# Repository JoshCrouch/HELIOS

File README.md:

# HELIOS
A basic SDR Project to practice designing an RF Front-End

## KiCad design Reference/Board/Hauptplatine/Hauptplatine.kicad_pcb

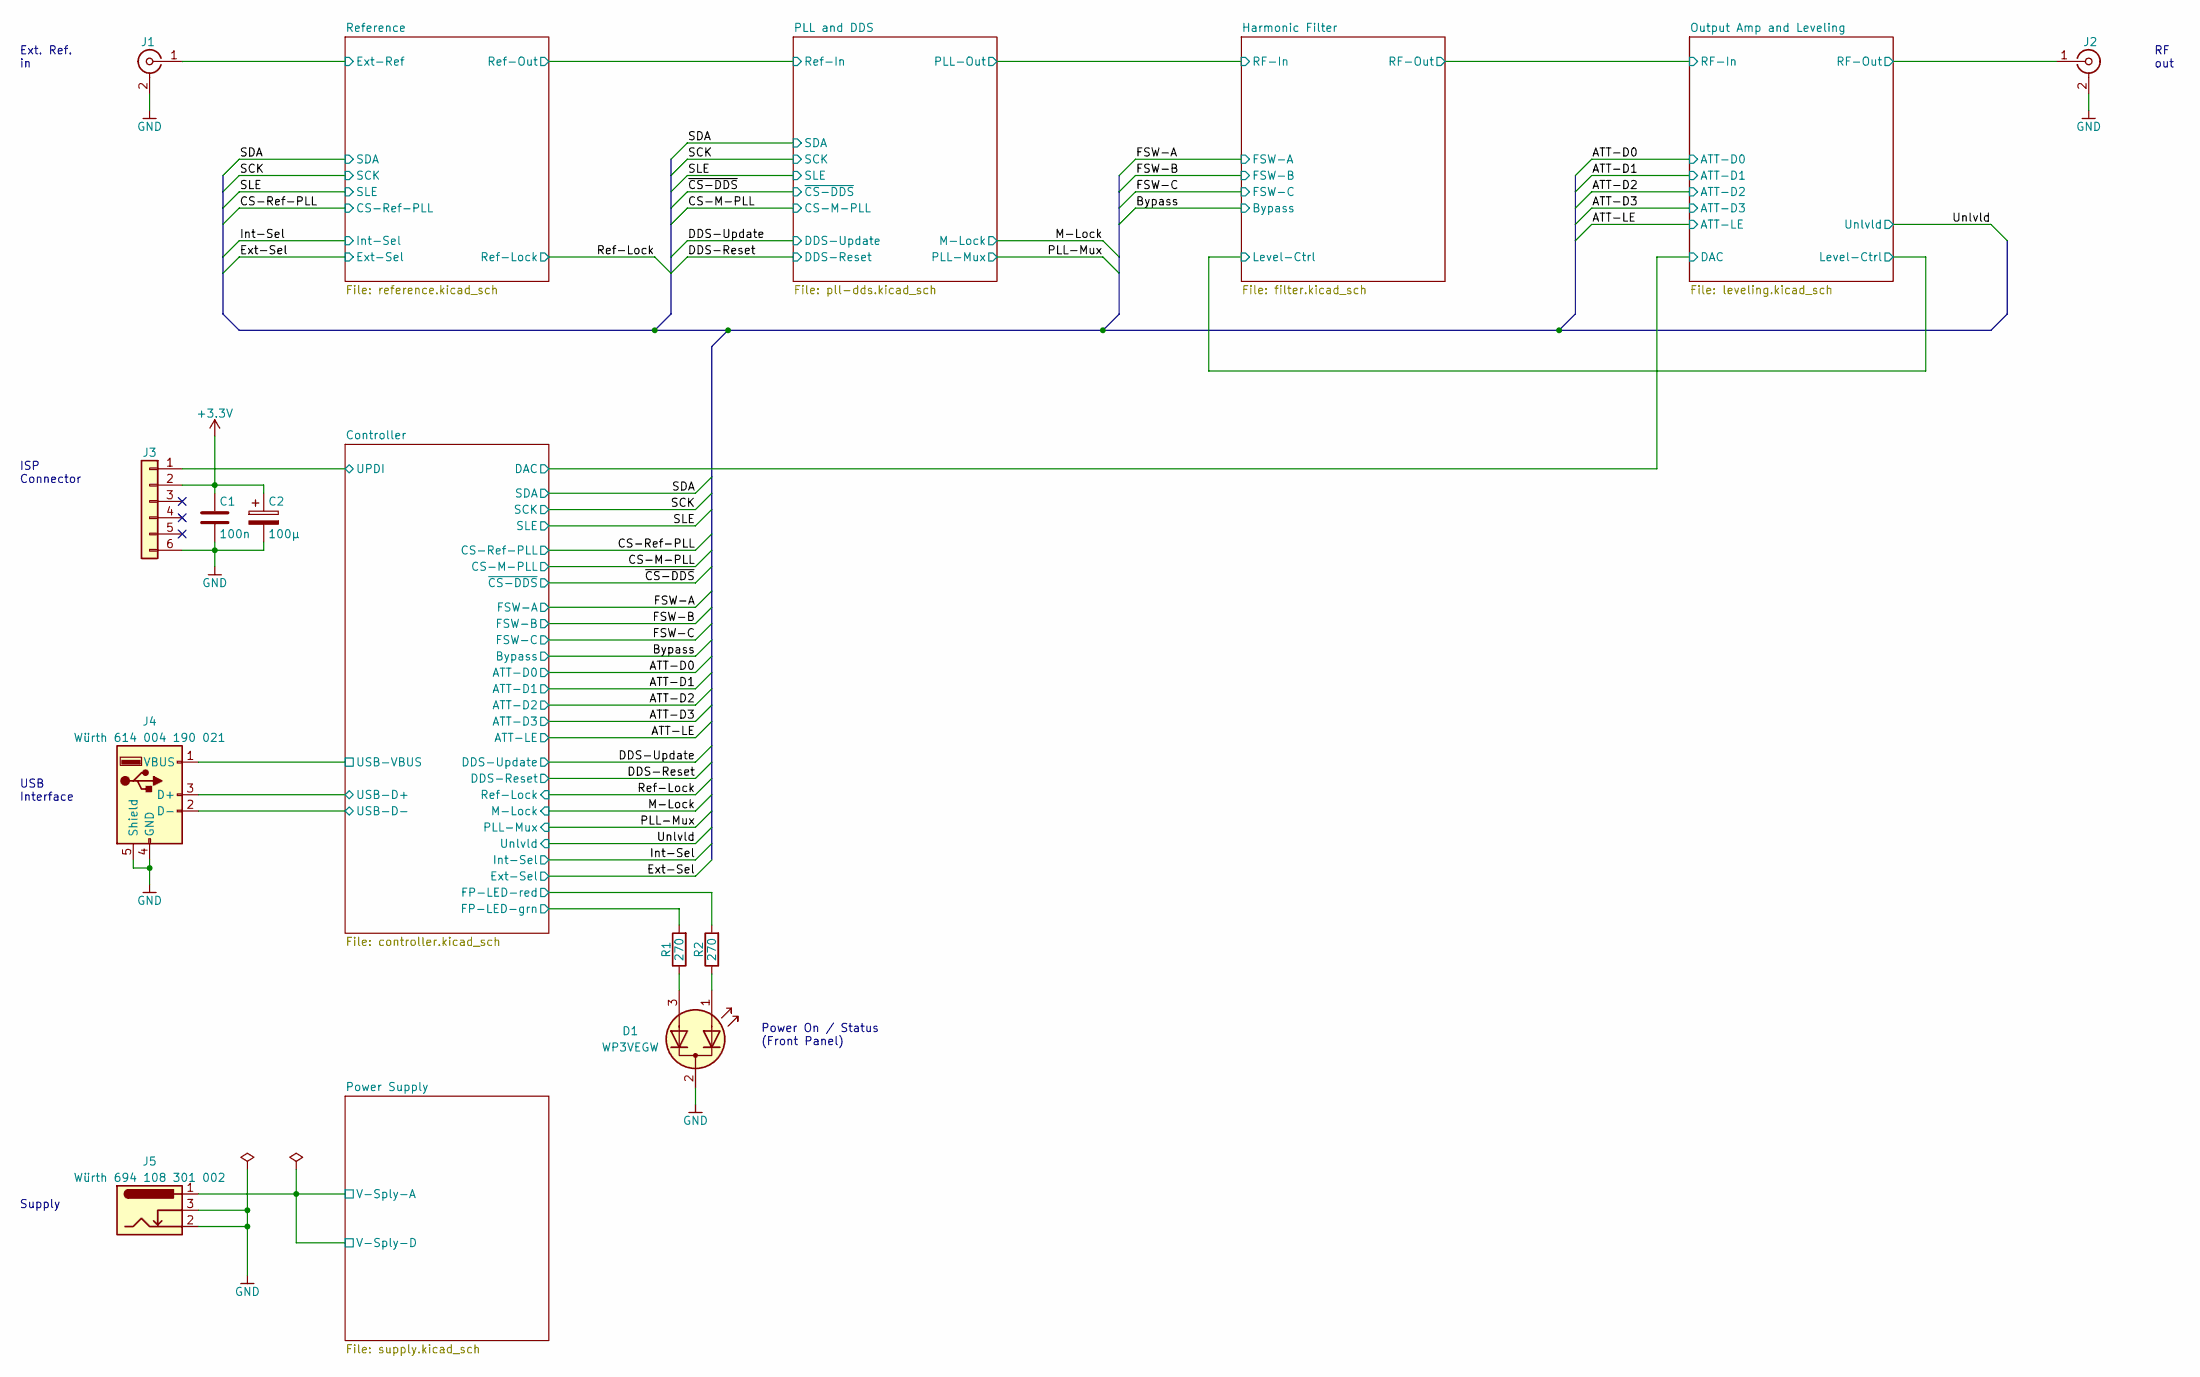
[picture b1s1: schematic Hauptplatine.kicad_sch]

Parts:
C1: 100n; C_0805_2012Metric
C2: 100µ; CP_Radial_D6.3mm_P2.50mm
D1: WP3VEGW; LED_D3.0mm-3
J1: SMA; SMA-Jack_angle
J2: Cinch 142-0781-821; SMA-Launcher_Cinch_142-0771-831
J3: Conn_01x06; IDC-Header_2x03_P2.54mm_Vertical
J4: Würth 614 004 190 021; USB_A_Stewart_SS-52100-001_Horizontal
J5: Würth 694 108 301 002; BarrelJack_Wuerth_6941xx301002
R1, R2: 270; R_0805_2012Metric

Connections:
/Controller/FP-LED-grn: R1.2; also elsewhere on the board
/Controller/FP-LED-red: R2.2; also elsewhere on the board
/Controller/UPDI: J3.1; also elsewhere on the board
/Controller/USB-D+: J4.3 (D+); also elsewhere on the board
/Controller/USB-D-: J4.2 (D-); also elsewhere on the board
/Controller/USB-VBUS: J4.1 (VBUS); also elsewhere on the board
/Output Amp and Leveling/RF-Out: J2.1 (In); also elsewhere on the board
/Power Supply/V-Sply-A: J5.1; also elsewhere on the board
/Reference/Ext-Ref: J1.1 (In); also elsewhere on the board
unnamed: D1.1 (A1), R2.1
unnamed: D1.3 (A2), R1.1

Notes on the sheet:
Supply
USB Interface
RF out
Power On / Status (Front Panel)
Ext. Ref. in
ISP Connector

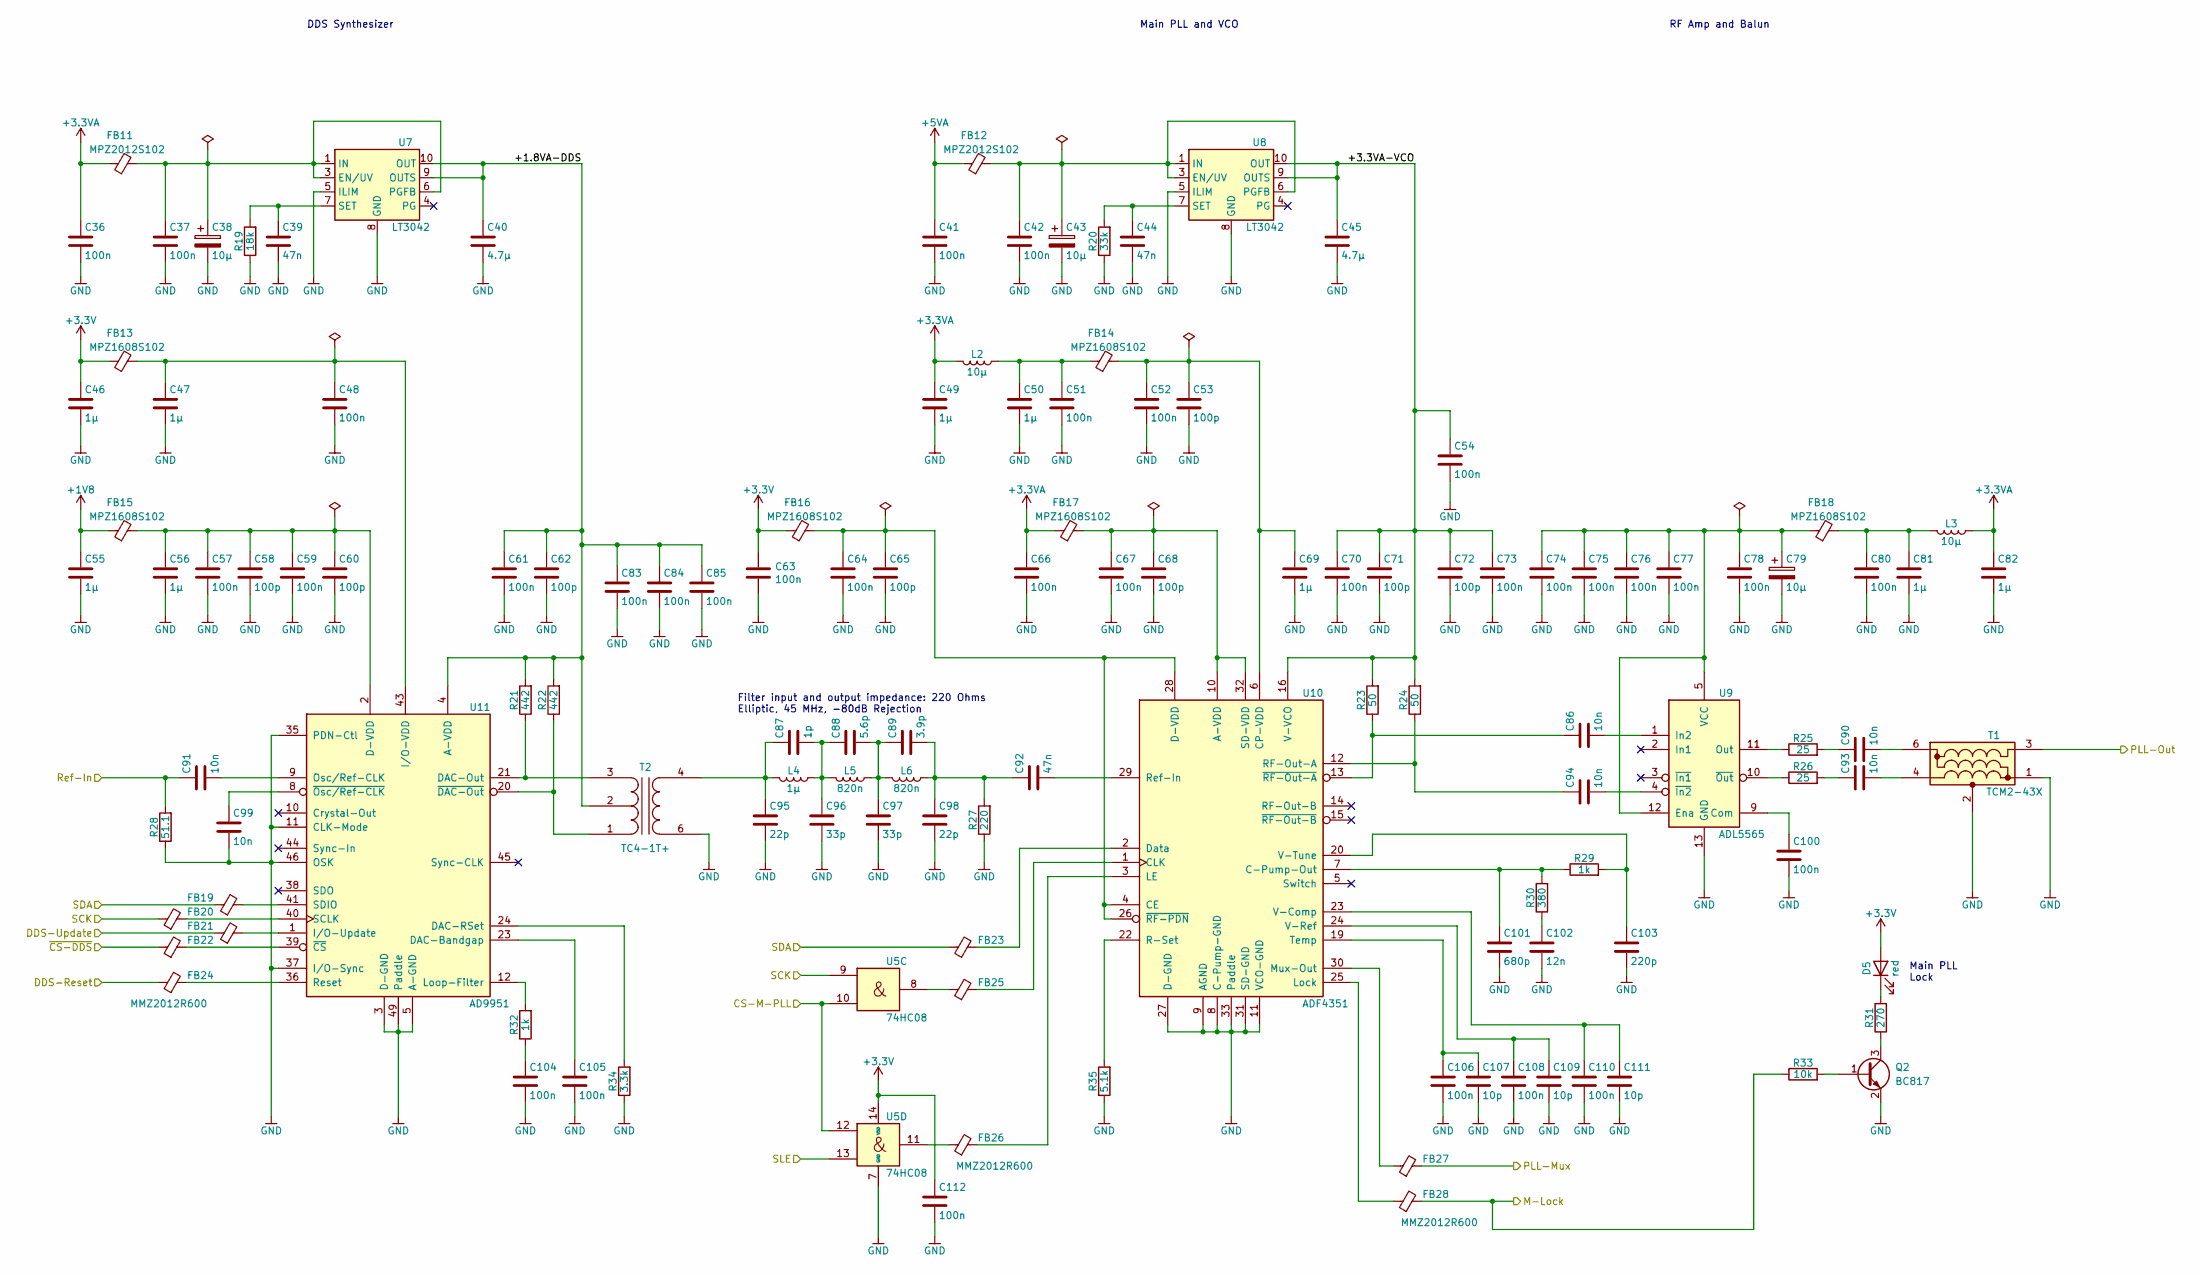
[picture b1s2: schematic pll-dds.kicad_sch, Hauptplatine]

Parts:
C36, C37, C41, C42, C112: 100n; C_0805_2012Metric
C38, C43, C79: 10µ; CP_EIA-3528-21_Kemet-B
C39, C44, C92: 47n; C_0805_2012Metric
C40, C45: 4.7µ; C_0805_2012Metric
C46, C47, C49, C50, C55, C56, C81, C82: 1µ; C_0603_1608Metric
C48, C51, C52, C54, C57, C59, C61, C63, C64, C66, C67, C70, C73, C74, C75, C76, C77, C78, C80, C83, C84, C85, C100, C104, C105, C106, C108, C110: 100n; C_0603_1608Metric
C53, C58, C60, C62, C65, C68, C71, C72: 100p; C_0603_1608Metric
C69: 1µ; C_0805_2012Metric
C86, C90, C91, C93, C94, C99: 10n; C_0603_1608Metric
C87: 1p; C_0805_2012Metric
C88: 5.6p; C_0805_2012Metric
C89: 3.9p; C_0805_2012Metric
C95, C98: 22p; C_0805_2012Metric
C96, C97: 33p; C_0805_2012Metric
C101: 680p; C_0603_1608Metric
C102: 12n; C_0603_1608Metric
C103: 220p; C_0603_1608Metric
C107, C109, C111: 10p; C_0603_1608Metric
D5: red; LED_0805_2012Metric
FB11, FB12: MPZ2012S102; L_0805_2012Metric
FB13, FB14, FB15, FB16, FB17, FB18: MPZ1608S102; L_0603_1608Metric
FB19, FB20, FB21, FB22, FB23, FB24, FB25, FB26, FB27, FB28: MMZ2012R600; L_0805_2012Metric
L2, L3: 10µ; L_0805_2012Metric
L4: 1µ; L_0805_2012Metric
L5, L6: 820n; L_0805_2012Metric
Q2: BC817; SOT-23
R19: 18k; R_0805_2012Metric
R20: 33k; R_0805_2012Metric
R21, R22: 442; R_0603_1608Metric
R23, R24: 50; R_0603_1608Metric
R25, R26: 25; R_0603_1608Metric
R27: 220; R_0805_2012Metric
R28: 51.1; R_0603_1608Metric
R29, R32: 1k; R_0603_1608Metric
R30: 380; R_0603_1608Metric
R31: 270; R_0805_2012Metric
R33: 10k; R_0805_2012Metric
R34: 3.3k; R_0603_1608Metric
R35: 5.1k; R_0603_1608Metric
T1: TCM2-43X; Mini-Circuits_DB1627
T2: TC4-1T+; Mini-Circuits_AT224-1
U5: 74HC08; SOIC-14_3.9x8.7mm_P1.27mm
U7, U8: LT3042; MSOP-10-1EP_3x3mm_P0.5mm_EP1.68x1.88mm
U9: ADL5565; QFN-16-1EP_3x3mm_P0.5mm_EP1.45x1.45mm_ThermalVias
U10: ADF4351; QFN-32-1EP_5x5mm_P0.5mm_EP3.1x3.1mm_ThermalVias
U11: AD9951; TQFP-48-1EP_7x7mm_P0.5mm_EP3.5x3.5mm

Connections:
+1V8: C55.1, FB15.1; also elsewhere on the board
+3.3VA: C36.1, C49.1, C66.1, C82.1, FB11.1, FB17.1, L2.2, L3.1; also elsewhere on the board
+5VA: C41.1, FB12.1; also elsewhere on the board
/CS-M-PLL: U5.10, U5.12; also elsewhere on the board
/DDS-Reset: FB24.1; also elsewhere on the board
/DDS-Update: FB21.1; also elsewhere on the board
/M-Lock: FB28.2, R33.1; also elsewhere on the board
/PLL and DDS/+1.8VA-DDS: C40.1, C61.1, C62.1, C83.1, C84.1, C85.1, R21.2, R22.2, T2.2 (SC), U7.9 (OUTS), U7.10 (OUT), U11.4 (A-VDD), U11.6 (A-VDD), U11.13 (A-VDD), U11.16 (A-VDD), U11.18 (A-VDD), U11.19 (A-VDD), U11.25 (A-VDD), U11.27 (A-VDD), U11.29 (A-VDD)
/PLL and DDS/+3.3VA-VCO: C45.1, C54.1, C70.1, C71.1, C72.1, C73.1, R23.2, R24.2, U8.9 (OUTS), U8.10 (OUT), U10.16 (V-VCO), U10.17 (V-VCO)
/PLL and DDS/PLL-Out: T1.3 (Pri_dot); also elsewhere on the board
/PLL and DDS/Ref-In: C91.1, R28.2; also elsewhere on the board
/PLL-Mux: FB27.2; also elsewhere on the board
/SCK: FB20.1, U5.9; also elsewhere on the board
/SDA: FB19.1, FB23.1; also elsewhere on the board
/SLE: U5.13; also elsewhere on the board
/~CS-DDS: FB22.1; also elsewhere on the board
unnamed: C37.1, C38.1, FB11.2, U7.1 (IN), U7.2 (IN), U7.3 (EN/UV), U7.6 (PGFB)
unnamed: C39.1, R19.2, U7.7 (SET)
unnamed: C42.1, C43.1, FB12.2, U8.1 (IN), U8.2 (IN), U8.3 (EN/UV), U8.6 (PGFB)
unnamed: C44.1, R20.2, U8.7 (SET)
unnamed: C47.1, C48.1, FB13.2, U11.43 (I/O-VDD)
unnamed: C50.1, C51.1, FB14.1, L2.1
unnamed: C52.1, C53.1, C69.1, FB14.2, U10.6 (CP-VDD)
unnamed: C56.1, C57.1, C58.1, C59.1, C60.1, FB15.2, U11.2 (D-VDD), U11.34 (D-VDD)
unnamed: C64.1, C65.1, FB16.2, U10.4 (CE), U10.26 (~RF-PDN), U10.28 (D-VDD)
unnamed: C67.1, C68.1, FB17.2, U10.10 (A-VDD), U10.32 (SD-VDD)
unnamed: C74.1, C75.1, C76.1, C77.1, C78.1, C79.1, FB18.1, U9.5 (VCC), U9.6 (VCC), U9.7 (VCC), U9.8 (VCC), U9.12 (Ena)
unnamed: C80.1, C81.1, FB18.2, L3.2
unnamed: C86.1, R23.1, U10.13 (~RF-Out-A)
unnamed: C86.2, U9.1 (In2)
unnamed: C87.1, C95.1, L4.2, T2.4 (AA)
unnamed: C87.2, C88.1, C96.1, L4.1, L5.2
unnamed: C88.2, C89.1, C97.1, L5.1, L6.2
unnamed: C89.2, C92.1, C98.1, L6.1, R27.2
unnamed: C90.1, R25.2
unnamed: C90.2, T1.6 (Sec-dot)
unnamed: C91.2, U11.9 (Osc/Ref-CLK)
unnamed: C92.2, U10.29 (Ref-In)
unnamed: C93.1, R26.2
unnamed: C93.2, T1.4 (Sec)
unnamed: C94.1, R24.1, U10.12 (RF-Out-A)
unnamed: C94.2, U9.4 (~In2)
unnamed: C99.1, U11.8 (~Osc/Ref-CLK)
unnamed: C100.1, U9.9 (Com)
unnamed: C101.1, R29.1, R30.2, U10.7 (C-Pump-Out)
unnamed: C102.1, R30.1
unnamed: C103.1, R29.2, U10.20 (V-Tune)
unnamed: C104.1, R32.1
unnamed: C105.1, U11.23 (DAC-Bandgap)
unnamed: C106.1, C107.1, U10.19 (Temp)
unnamed: C108.1, C109.1, U10.24 (V-Ref)
unnamed: C110.1, C111.1, U10.23 (V-Comp)
unnamed: D5.1 (K), R31.2
unnamed: FB19.2, U11.41 (SDIO)
unnamed: FB20.2, U11.40 (SCLK)
unnamed: FB21.2, U11.1 (I/O-Update)
unnamed: FB22.2, U11.39 (~CS)
unnamed: FB23.2, U10.2 (Data)
unnamed: FB24.2, U11.36 (Reset)
unnamed: FB25.1, U5.8
unnamed: FB25.2, U10.1 (CLK)
unnamed: FB26.1, U5.11
unnamed: FB26.2, U10.3 (LE)
unnamed: FB27.1, U10.30 (Mux-Out)
unnamed: FB28.1, U10.25 (Lock)
unnamed: Q2.1 (B), R33.2
unnamed: Q2.3 (C), R31.1
unnamed: R21.1, T2.3 (SB), U11.21 (DAC-Out)
unnamed: R22.1, T2.1 (SA), U11.20 (~DAC-Out)
unnamed: R25.1, U9.11 (Out)
unnamed: R26.1, U9.10 (~Out)
unnamed: R32.2, U11.12 (Loop-Filter)
unnamed: R34.2, U11.24 (DAC-RSet)
unnamed: R35.2, U10.22 (R-Set)

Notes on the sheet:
Filter input and output impedance: 220 Ohms Elliptic, 45 MHz, -80dB Rejection
RF Amp and Balun
Main PLL and VCO
DDS Synthesizer
Main PLL Lock

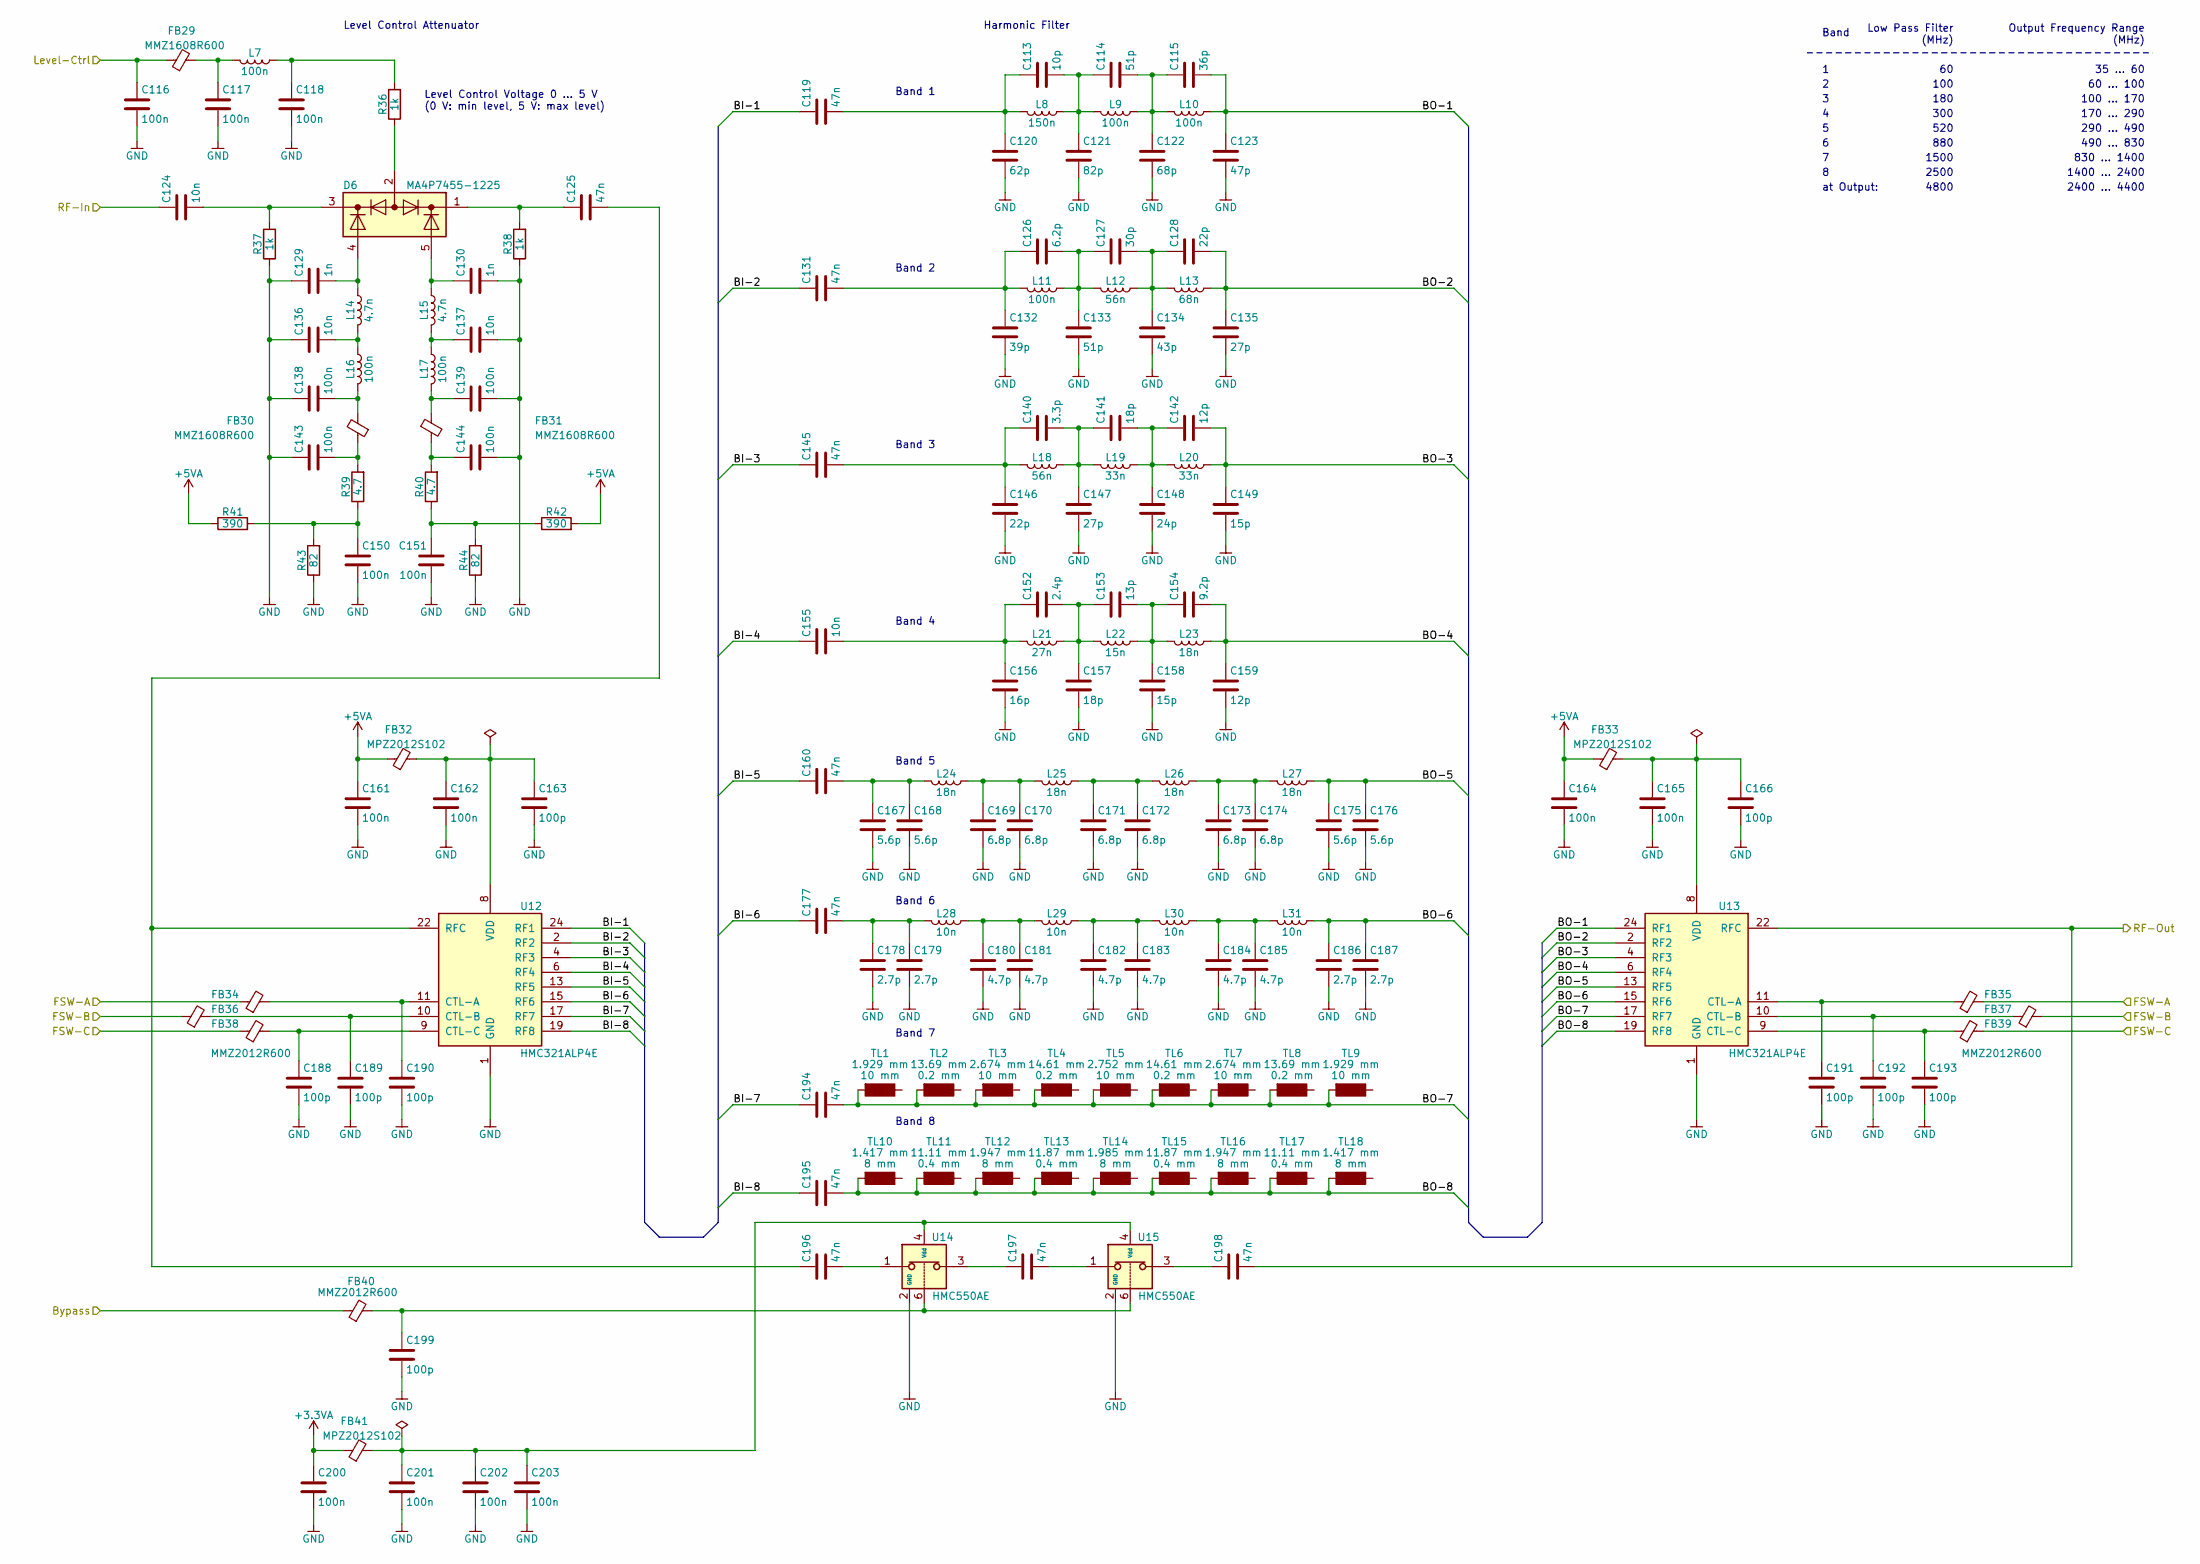
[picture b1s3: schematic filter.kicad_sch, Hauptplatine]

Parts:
C113: 10p; C_0603_1608Metric
C114, C133: 51p; C_0603_1608Metric
C115: 36p; C_0603_1608Metric
C116, C117, C118, C138, C139, C143, C144, C150, C151, C161, C162, C164, C165, C200, C201, C202, C203: 100n; C_0603_1608Metric
C119, C125, C131, C145, C160, C177, C194, C195, C196, C197, C198: 47n; C_0603_1608Metric
C120: 62p; C_0603_1608Metric
C121: 82p; C_0603_1608Metric
C122: 68p; C_0603_1608Metric
C123: 47p; C_0603_1608Metric
C124, C136, C137, C155: 10n; C_0603_1608Metric
C126: 6.2p; C_0603_1608Metric
C127: 30p; C_0603_1608Metric
C128, C146: 22p; C_0603_1608Metric
C129, C130: 1n; C_0603_1608Metric
C132: 39p; C_0603_1608Metric
C134: 43p; C_0603_1608Metric
C135, C147: 27p; C_0603_1608Metric
C140: 3.3p; C_0603_1608Metric
C141, C157: 18p; C_0603_1608Metric
C142, C159: 12p; C_0603_1608Metric
C148: 24p; C_0603_1608Metric
C149, C158: 15p; C_0603_1608Metric
C152: 2.4p; C_0603_1608Metric
C153: 13p; C_0603_1608Metric
C154: 9.2p; C_0603_1608Metric
C156: 16p; C_0603_1608Metric
C163, C166: 100p; C_0603_1608Metric
C167, C168, C175, C176: 5.6p; C_0603_1608Metric
C169, C170, C171, C172, C173, C174: 6.8p; C_0603_1608Metric
C178, C179, C186, C187: 2.7p; C_0603_1608Metric
C180, C181, C182, C183, C184, C185: 4.7p; C_0603_1608Metric
C188, C189, C190, C191, C192, C193, C199: 100p; C_0805_2012Metric
D6: MA4P7455-1225; SOT-23-5
FB29, FB30, FB31: MMZ1608R600; L_0603_1608Metric
FB32, FB33, FB41: MPZ2012S102; L_0805_2012Metric
FB34, FB35, FB36, FB37, FB38, FB39, FB40: MMZ2012R600; L_0805_2012Metric
L7, L9, L10, L11, L16, L17: 100n; L_0603_1608Metric
L8: 150n; L_0603_1608Metric
L12, L18: 56n; L_0603_1608Metric
L13: 68n; L_0603_1608Metric
L14, L15: 4.7n; L_0603_1608Metric
L19, L20: 33n; L_0603_1608Metric
L21: 27n; L_0603_1608Metric
L22: 15n; L_0603_1608Metric
L23, L24, L25, L26, L27: 18n; L_0603_1608Metric
L28, L29, L30, L31: 10n; L_0603_1608Metric
R36, R37, R38: 1k; R_0603_1608Metric
R39, R40: 4.7; R_0603_1608Metric
R41, R42: 390; R_0805_2012Metric
R43, R44: 82; R_0805_2012Metric
TL1, TL9: 1.929 mm; Transline
TL2, TL8: 13.69 mm; Transline
TL3, TL7: 2.674 mm; Transline
TL4, TL6: 14.61 mm; Transline
TL5: 2.752 mm; Transline
TL10, TL18: 1.417 mm; Transline
TL11, TL17: 11.11 mm; Transline
TL12, TL16: 1.947 mm; Transline
TL13, TL15: 11.87 mm; Transline
TL14: 1.985 mm; Transline
U12, U13: HMC321ALP4E; QFN-24-1EP_4x4mm_P0.5mm_EP2.7x2.7mm_ThermalVias
U14, U15: HMC550AE; SOT-23-6

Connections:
+3.3VA: C200.1, FB41.1; also elsewhere on the board
+5VA: C161.1, C164.1, FB32.1, FB33.1, R41.1, R42.2; also elsewhere on the board
/Bypass: FB40.1; also elsewhere on the board
/FSW-A: FB34.1, FB35.2; also elsewhere on the board
/FSW-B: FB36.1, FB37.2; also elsewhere on the board
/FSW-C: FB38.1, FB39.2; also elsewhere on the board
/Harmonic Filter/BI-1: C119.1, U12.24 (RF1)
/Harmonic Filter/BI-2: C131.1, U12.2 (RF2)
/Harmonic Filter/BI-3: C145.1, U12.4 (RF3)
/Harmonic Filter/BI-4: C155.1, U12.6 (RF4)
/Harmonic Filter/BI-5: C160.1, U12.13 (RF5)
/Harmonic Filter/BI-6: C177.1, U12.15 (RF6)
/Harmonic Filter/BI-7: C194.1, U12.17 (RF7)
/Harmonic Filter/BI-8: C195.1, U12.19 (RF8)
/Harmonic Filter/BO-1: C115.2, C123.1, L10.1, U13.24 (RF1)
/Harmonic Filter/BO-2: C128.2, C135.1, L13.1, U13.2 (RF2)
/Harmonic Filter/BO-3: C142.2, C149.1, L20.1, U13.4 (RF3)
/Harmonic Filter/BO-4: C154.2, C159.1, L23.1, U13.6 (RF4)
/Harmonic Filter/BO-5: C175.1, C176.1, L27.1, U13.13 (RF5)
/Harmonic Filter/BO-6: C186.1, C187.1, L31.1, U13.15 (RF6)
/Harmonic Filter/BO-7: C194.2, TL1.1, TL2.1, TL3.1, TL4.1, TL5.1, TL6.1, TL7.1, TL8.1, TL9.1, U13.17 (RF7)
/Harmonic Filter/BO-8: C195.2, TL10.1, TL11.1, TL12.1, TL13.1, TL14.1, TL15.1, TL16.1, TL17.1, TL18.1, U13.19 (RF8)
/Harmonic Filter/Level-Ctrl: C116.1, FB29.1; also elsewhere on the board
/Output Amp and Leveling/RF-In: C198.2, U13.22 (RFC); also elsewhere on the board
/PLL and DDS/PLL-Out: C124.1; also elsewhere on the board
unnamed: C113.1, C119.2, C120.1, L8.2
unnamed: C113.2, C114.1, C121.1, L8.1, L9.2
unnamed: C114.2, C115.1, C122.1, L9.1, L10.2
unnamed: C117.1, FB29.2, L7.2
unnamed: C118.1, L7.1, R36.2
unnamed: C124.2, D6.3 (RF_out), R37.2
unnamed: C125.1, D6.1 (RF_in), R38.2
unnamed: C125.2, C196.1, U12.22 (RFC)
unnamed: C126.1, C131.2, C132.1, L11.2
unnamed: C126.2, C127.1, C133.1, L11.1, L12.2
unnamed: C127.2, C128.1, C134.1, L12.1, L13.2
unnamed: C129.2, D6.4 (Shunt_Bias_2), L14.1
unnamed: C130.1, D6.5 (Shunt_Bias_1), L15.1
unnamed: C136.2, L14.2, L16.1
unnamed: C137.1, L15.2, L17.1
unnamed: C138.2, FB30.2, L16.2
unnamed: C139.1, FB31.1, L17.2
unnamed: C140.1, C145.2, C146.1, L18.2
unnamed: C140.2, C141.1, C147.1, L18.1, L19.2
unnamed: C141.2, C142.1, C148.1, L19.1, L20.2
unnamed: C143.2, FB30.1, R39.2
unnamed: C144.1, FB31.2, R40.2
unnamed: C150.1, R39.1, R41.2, R43.2
unnamed: C151.1, R40.1, R42.1, R44.2
unnamed: C152.1, C155.2, C156.1, L21.2
unnamed: C152.2, C153.1, C157.1, L21.1, L22.2
unnamed: C153.2, C154.1, C158.1, L22.1, L23.2
unnamed: C160.2, C167.1, C168.1, L24.2
unnamed: C162.1, C163.1, FB32.2, U12.8 (VDD)
unnamed: C165.1, C166.1, FB33.2, U13.8 (VDD)
unnamed: C169.1, C170.1, L24.1, L25.2
unnamed: C171.1, C172.1, L25.1, L26.2
unnamed: C173.1, C174.1, L26.1, L27.2
unnamed: C177.2, C178.1, C179.1, L28.2
unnamed: C180.1, C181.1, L28.1, L29.2
unnamed: C182.1, C183.1, L29.1, L30.2
unnamed: C184.1, C185.1, L30.1, L31.2
unnamed: C188.1, FB38.2, U12.9 (CTL-C)
unnamed: C189.1, FB36.2, U12.10 (CTL-B)
unnamed: C190.1, FB34.2, U12.11 (CTL-A)
unnamed: C191.1, FB35.1, U13.11 (CTL-A)
unnamed: C192.1, FB37.1, U13.10 (CTL-B)
unnamed: C193.1, FB39.1, U13.9 (CTL-C)
unnamed: C196.2, U14.1
unnamed: C197.1, U14.3
unnamed: C197.2, U15.1
unnamed: C198.1, U15.3
unnamed: C199.1, FB40.2, U14.6, U15.6
unnamed: C201.1, C202.1, C203.1, FB41.2, U14.4 (Vdd), U15.4 (Vdd)
unnamed: D6.2 (Ser_Bias), R36.1

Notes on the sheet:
Harmonic Filter
Level Control Attenuator
Band 1
520
Low Pass Filter (MHz)
300
Band 2
1400 ... 2400
180
830 ... 1400
4800
Band 5
Band
2400 ... 4400
Band 3
Band 8
Band 6
100 ... 170
490 ... 830
Band 7
Output Frequency Range (MHz)
Band 4
170 ... 290
Level Control Voltage 0 ... 5 V (0 V: min level, 5 V: max level)
at Output:
880
100
35 ... 60
1500
60 ... 100
290 ... 490
2500

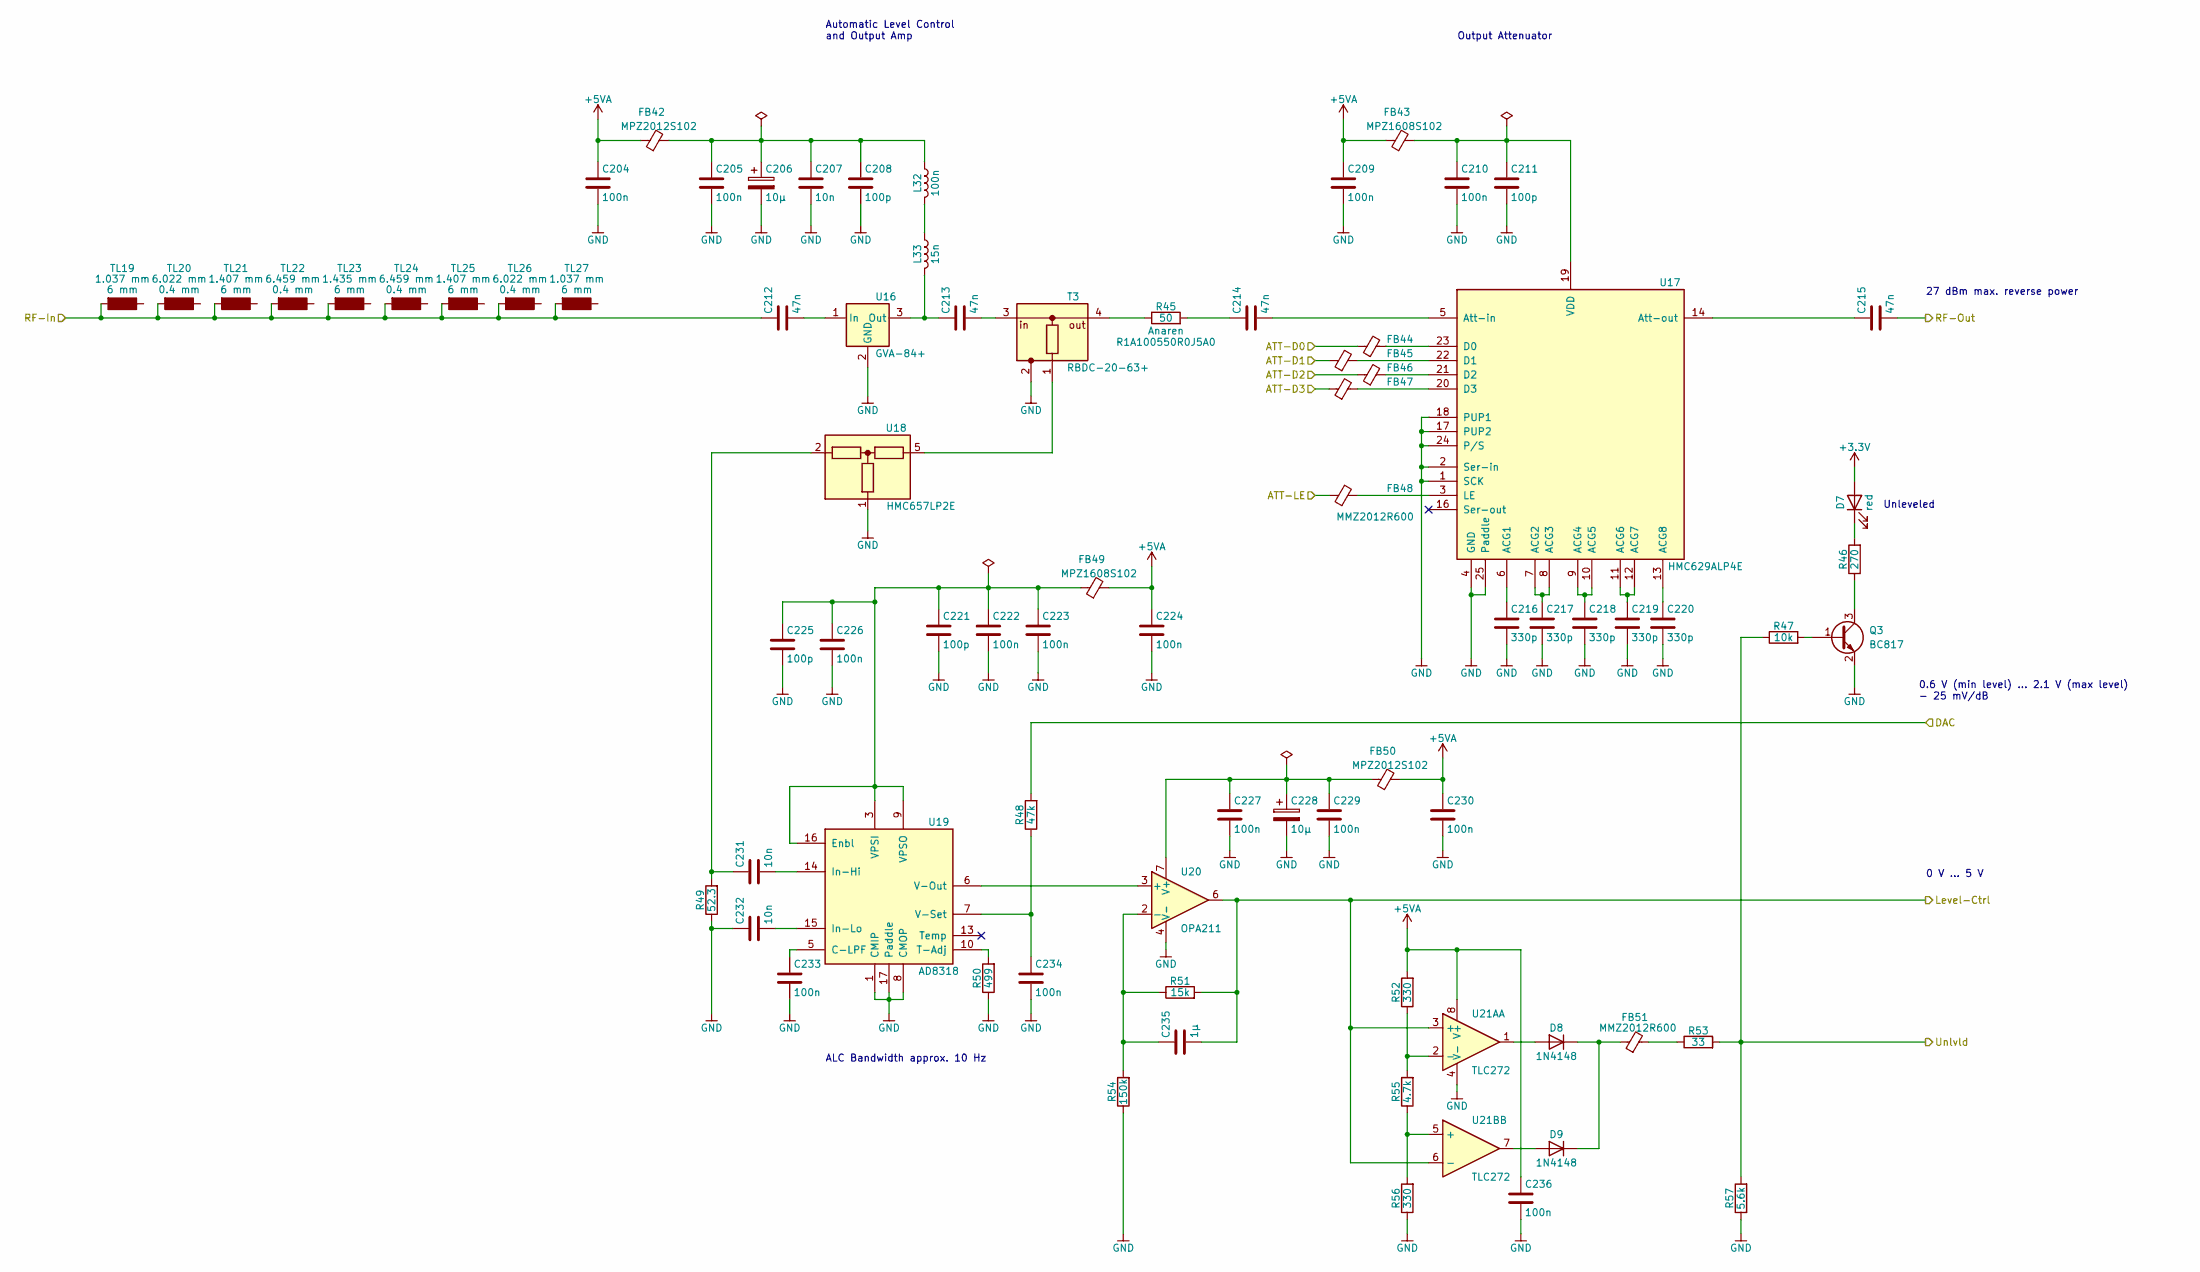
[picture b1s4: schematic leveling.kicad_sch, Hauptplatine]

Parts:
C204, C205, C227, C229, C230, C236: 100n; C_0805_2012Metric
C206, C228: 10µ; CP_EIA-3528-21_Kemet-B
C207: 10n; C_0805_2012Metric
C208, C211, C221, C225: 100p; C_0603_1608Metric
C209, C210, C222, C223, C224, C226, C233, C234: 100n; C_0603_1608Metric
C212, C213, C214, C215: 47n; C_0603_1608Metric
C216, C217, C218, C219, C220: 330p; C_0603_1608Metric
C231, C232: 10n; C_0603_1608Metric
C235: 1µ; C_0805_2012Metric
D7: red; LED_0805_2012Metric
D8, D9: 1N4148; D_SOD-323F
FB42, FB50: MPZ2012S102; L_0805_2012Metric
FB43, FB49: MPZ1608S102; L_0603_1608Metric
FB44, FB45, FB46, FB47, FB48, FB51: MMZ2012R600; L_0805_2012Metric
L32: 100n; L_0603_1608Metric
L33: 15n; L_0603_1608Metric
Q3: BC817; SOT-23
R45: 50; R_0402_1005Metric; Part No R1A100550R0J5A0
R46: 270; R_0805_2012Metric
R47: 10k; R_0805_2012Metric
R48: 47k; R_0603_1608Metric
R49: 52.3; R_0603_1608Metric
R50: 499; R_0603_1608Metric
R51: 15k; R_0805_2012Metric
R52, R56: 330; R_0805_2012Metric
R53: 33; R_0805_2012Metric
R54: 150k; R_0805_2012Metric
R55: 4.7k; R_0805_2012Metric
R57: 5.6k; R_0805_2012Metric
T3: RBDC-20-63+; Mini-Circuits_TT1224-2
TL19, TL27: 1.037 mm; Transline
TL20, TL26: 6.022 mm; Transline
TL21, TL25: 1.407 mm; Transline
TL22, TL24: 6.459 mm; Transline
TL23: 1.435 mm; Transline
U16: GVA-84+; SOT-89-3
U17: HMC629ALP4E; QFN-24-1EP_4x4mm_P0.5mm_EP2.6x2.6mm_ThermalVias
U18: HMC657LP2E; DFN-6-1EP_2x2mm_P0.5mm_EP0.61x1.42mm
U19: AD8318; QFN-16-1EP_4x4mm_P0.65mm_EP2.1x2.1mm_ThermalVias
U20: OPA211; SOIC-8_3.9x4.9mm_P1.27mm
U21A, U21B, U21C: TLC272; SOIC-8_3.9x4.9mm_P1.27mm

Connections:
+5VA: C204.1, C209.1, C224.1, C230.1, C236.1, FB42.1, FB43.1, FB49.2, FB50.2, R52.2, U21C.8 (V+); also elsewhere on the board
/ATT-D0: FB44.1; also elsewhere on the board
/ATT-D1: FB45.1; also elsewhere on the board
/ATT-D2: FB46.1; also elsewhere on the board
/ATT-D3: FB47.1; also elsewhere on the board
/ATT-LE: FB48.1; also elsewhere on the board
/Controller/DAC: R48.2; also elsewhere on the board
/Harmonic Filter/Level-Ctrl: C235.2, R51.2, U20.6, U21A.3 (+), U21B.6 (-); also elsewhere on the board
/Output Amp and Leveling/RF-In: C212.1, TL19.1, TL20.1, TL21.1, TL22.1, TL23.1, TL24.1, TL25.1, TL26.1, TL27.1; also elsewhere on the board
/Output Amp and Leveling/RF-Out: C215.2; also elsewhere on the board
/Unlvld: R47.1, R53.2, R57.2; also elsewhere on the board
unnamed: C205.1, C206.1, C207.1, C208.1, FB42.2, L32.1
unnamed: C210.1, C211.1, FB43.2, U17.19 (VDD)
unnamed: C212.2, U16.1 (In)
unnamed: C213.1, L33.2, U16.3 (Out)
unnamed: C213.2, T3.3 (In)
unnamed: C214.1, R45.2
unnamed: C214.2, U17.5 (Att-in)
unnamed: C215.1, U17.14 (Att-out)
unnamed: C216.1, U17.6 (ACG1)
unnamed: C217.1, U17.7 (ACG2), U17.8 (ACG3)
unnamed: C218.1, U17.9 (ACG4), U17.10 (ACG5)
unnamed: C219.1, U17.11 (ACG6), U17.12 (ACG7)
unnamed: C220.1, U17.13 (ACG8)
unnamed: C227.1, C228.1, C229.1, FB50.1, U20.7 (V+)
unnamed: C231.1, R49.2, U18.2 (RF-in)
unnamed: C231.2, U19.14 (In-Hi)
unnamed: C232.2, U19.15 (In-Lo)
unnamed: C233.1, U19.5 (C-LPF)
unnamed: C234.1, R48.1, U19.7 (V-Set)
unnamed: C235.1, R51.1, R54.2, U20.2 (-)
unnamed: D7.1 (K), R46.2
unnamed: D8.1 (K), D9.1 (K), FB51.1
unnamed 207: D8.2 (A), U21A.1; also elsewhere on the board
unnamed 208: D9.2 (A), U21B.7; also elsewhere on the board
unnamed: FB44.2, U17.23 (D0)
unnamed: FB45.2, U17.22 (D1)
unnamed: FB46.2, U17.21 (D2)
unnamed: FB47.2, U17.20 (D3)
unnamed: FB48.2, U17.3 (LE)
unnamed: FB51.2, R53.1
unnamed: L32.2, L33.1
unnamed: Q3.1 (B), R47.2
unnamed: Q3.3 (C), R46.1
unnamed: R45.1, T3.4 (Out)
unnamed: R50.2, U19.10 (T-Adj)
unnamed 264: R52.1, R55.2, U21A.2 (-); also elsewhere on the board
unnamed 265: R55.1, R56.2, U21B.5 (+); also elsewhere on the board
unnamed: T3.1 (Coupled), U18.5 (RF-out)
unnamed: U19.6 (V-Out), U20.3 (+)
VPSI: C221.1, C222.1, C223.1, C225.1, C226.1, FB49.1, U19.3 (VPSI), U19.4 (VPSI), U19.9 (VPSO), U19.16 (Enbl)

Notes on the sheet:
0 V ... 5 V
Unleveled
ALC Bandwidth approx. 10 Hz
Output Attenuator
Automatic Level Control and Output Amp
0.6 V (min level) ... 2.1 V (max level) - 25 mV/dB
27 dBm max. reverse power
